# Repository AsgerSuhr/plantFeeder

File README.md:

# plantFeeder
A device that will water my plants when i'm not at home

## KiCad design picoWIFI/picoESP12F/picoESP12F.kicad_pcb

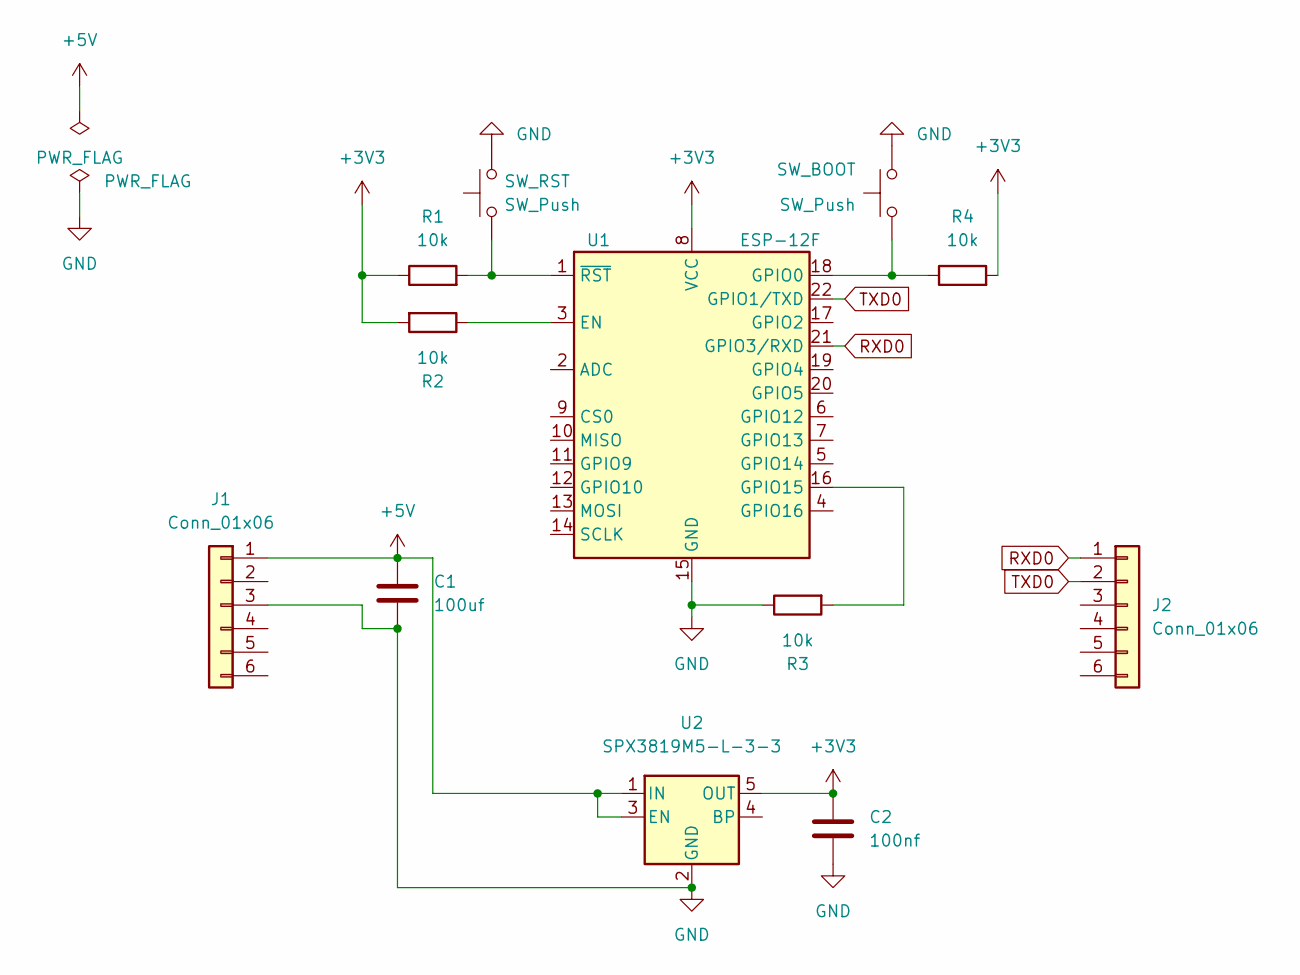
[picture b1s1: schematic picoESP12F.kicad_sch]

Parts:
C1: 100uf; C_0805_2012Metric; JLCPCB Part C141660
C2: 100nf; C_0805_2012Metric; JLCPCB Part C49678
J1, J2: Conn_01x06; PinHeader_1x06_P2.54mm_Vertical
R1, R2, R3, R4: 10k; R_1206_3216Metric; JLCPCB Part C17902
SW_BOOT: SW_Push; SW_Push_1P1T_NO_CK_KMR2; JLCPCB Part C269272
SW_RST: SW_Push; SW_Push_1P1T_NO_CK_KMR2; JLCPCB Part C269272
U1: ESP-12F; ESP-12E; JLCPCB Part C82891
U2: SPX3819M5-L-3-3; SOT-23-5; JLCPCB Part C9055

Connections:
+3V3: C2.1, R1.1, R2.2, R4.2, U1.8 (VCC), U2.5 (OUT)
+5V: C1.1, J1.1, U2.1 (IN), U2.3 (EN)
GND: C1.2, C2.2, J1.3, R3.1, SW_BOOT.1, SW_RST.2, U1.15 (GND), U2.2 (GND)
unnamed: R1.2, SW_RST.1, U1.1 (~RST)
unnamed: R2.1, U1.3 (EN)
unnamed: R3.2, U1.16 (GPIO15)
unnamed: R4.1, SW_BOOT.2, U1.18 (GPIO0)
RXD0: J2.1, U1.21 (GPIO3/RXD)
TXD0: J2.2, U1.22 (GPIO1/TXD)

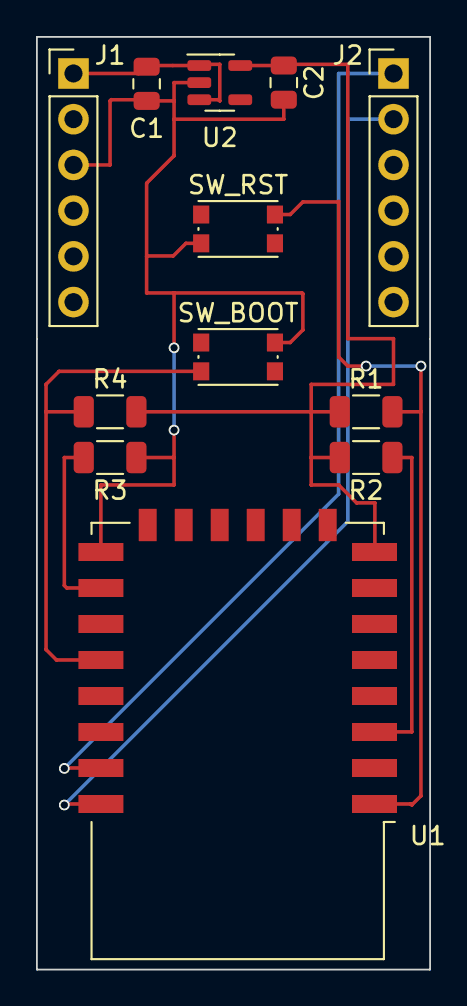
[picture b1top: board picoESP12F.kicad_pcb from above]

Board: 2 copper layers, 21.8 x 51.8 mm, 12 parts (0 on the bottom side), 9 nets.

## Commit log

2022-06-09 setup project
2022-06-16 small change
2022-06-17 test
2022-06-17 removed
2022-06-17 removed submodule
2022-06-17 removed submoduel
2022-06-17 removed submodules
2022-06-17 added esp lib
2022-06-18 removing unnecessary module
2022-06-25 testing with python, running out of time
2022-06-25 python
2022-06-26 pico wifi module design
    pico wifi module design
2022-07-05 working version, needs a lot of refinement tho'
2022-07-23 doing it in python
2022-07-24 fine adjustments
2022-07-24 testing
2022-07-28 optimized for pico w
2022-09-14 pumpModel
